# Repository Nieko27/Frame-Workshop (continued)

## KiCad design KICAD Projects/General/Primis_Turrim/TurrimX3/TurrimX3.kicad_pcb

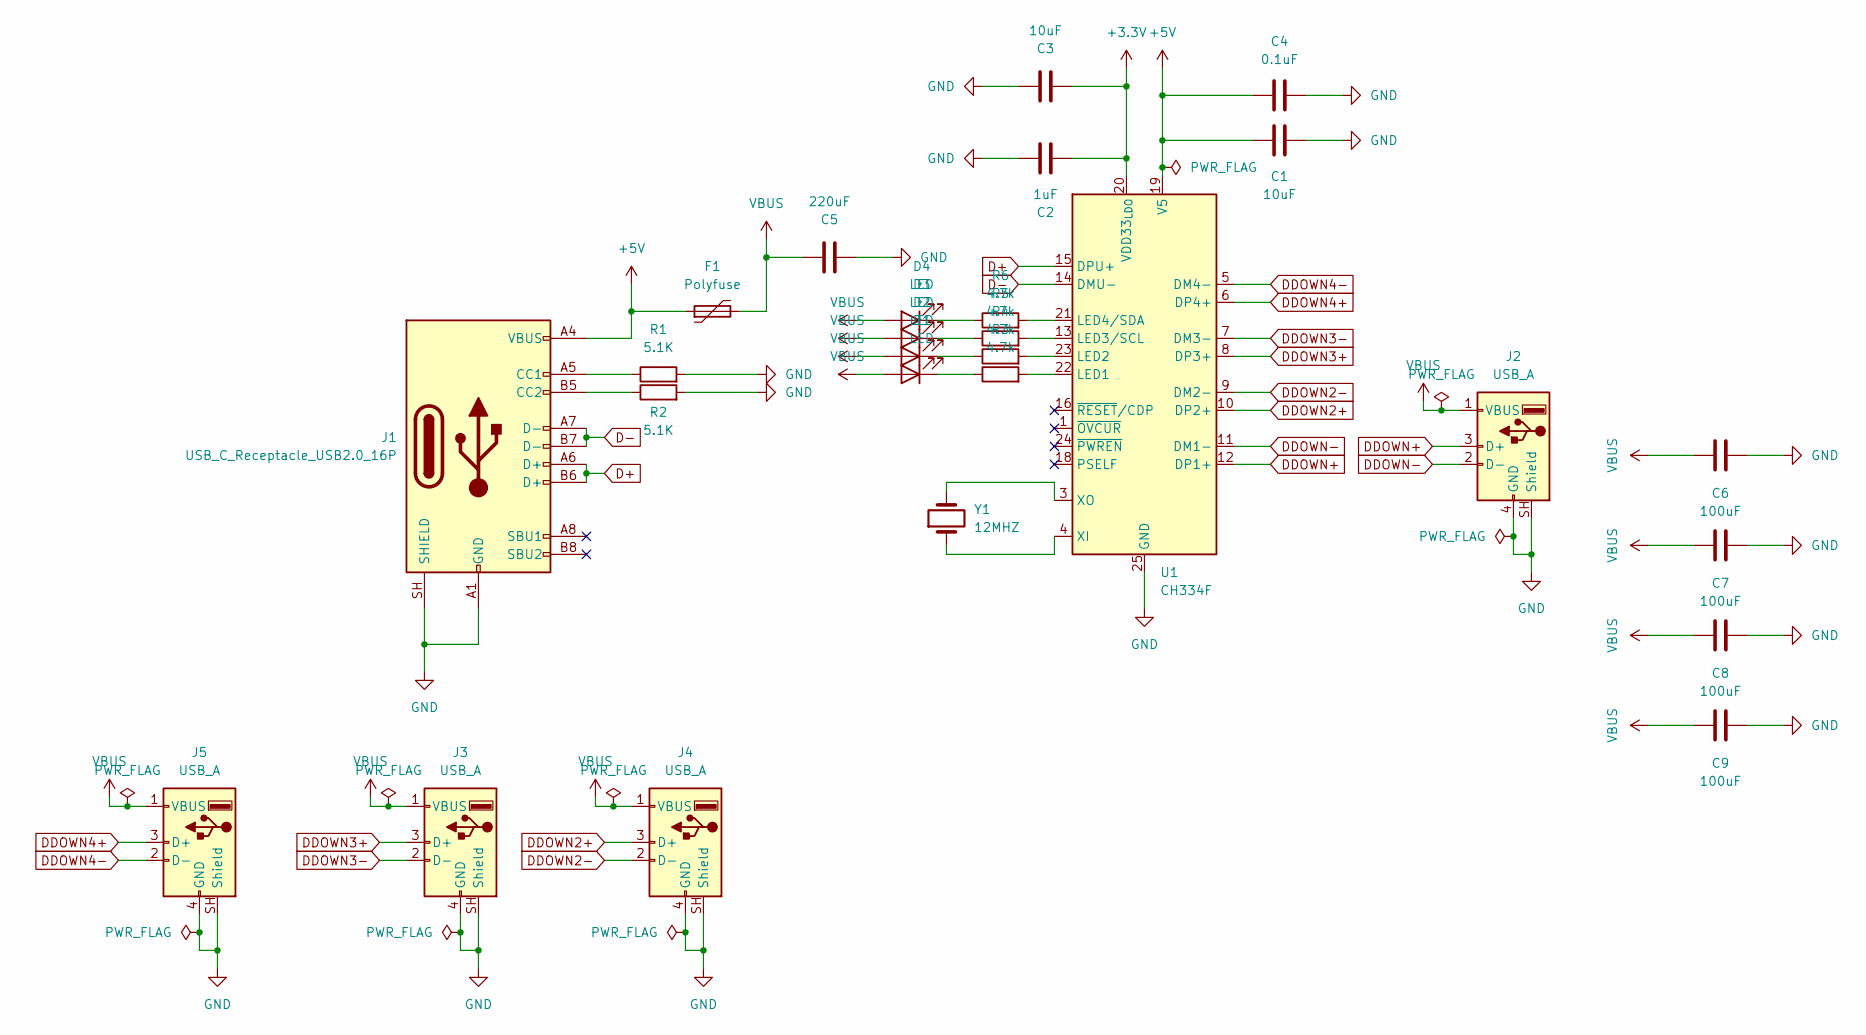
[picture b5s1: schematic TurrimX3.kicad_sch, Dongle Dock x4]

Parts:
C1, C3: 10uF; C_0805_2012Metric
C2: 1uF; C_0603_1608Metric
C4: 0.1uF; C_0603_1608Metric
C5: 220uF; C_0805_2012Metric
C6, C7, C8, C9: 100uF; C_0805_2012Metric
D1, D2, D3, D4: LED; LED_0603_1608Metric
F1: Polyfuse; Fuse_1206_3216Metric
J1: USB_C_Receptacle_USB2.0_16P; USB_C_Receptacle_HRO_TYPE-C-31-M-12
J2, J3, J4, J5: USB_A; USB_A_Molex_105057_Vertical
R1, R2: 5.1K; R_0805_2012Metric
R3, R4, R5, R6: 4.7k; R_0805_2012Metric
U1: CH334F; QFN-24-1EP_4x4mm_P0.5mm_EP2.7x2.7mm
Y1: 12MHZ; Crystal_SMD_2016-4Pin_2.0x1.6mm

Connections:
+3.3V: C2.1, C3.1, U1.20 (VDD33_{LDO})
+5V: C1.1, C4.1, F1.1, J1.A4 (VBUS), J1.A9 (VBUS), J1.B4 (VBUS), J1.B9 (VBUS), U1.19 (V5)
D+: J1.A6 (D+), J1.B6 (D+), U1.15 (DPU+)
D-: J1.A7 (D-), J1.B7 (D-), U1.14 (DMU-)
DDOWN2+: J4.3 (D+), U1.10 (DP2+)
DDOWN2-: J4.2 (D-), U1.9 (DM2-)
DDOWN3+: J3.3 (D+), U1.8 (DP3+)
DDOWN3-: J3.2 (D-), U1.7 (DM3-)
DDOWN4+: J5.3 (D+), U1.6 (DP4+)
DDOWN4-: J5.2 (D-), U1.5 (DM4-)
DDOWN+: J2.3 (D+), U1.12 (DP1+)
DDOWN-: J2.2 (D-), U1.11 (DM1-)
GND: C1.2, C2.2, C3.2, C4.2, C5.1, C6.2, C7.2, C8.2, C9.2, J1.A1 (GND), J1.A12 (GND), J1.B1 (GND), J1.B12 (GND), J1.SH (SHIELD), J2.4 (GND), J2.SH (Shield), J3.4 (GND), J3.SH (Shield), J4.4 (GND), J4.SH (Shield), J5.4 (GND), J5.SH (Shield), R1.2, R2.2, U1.25 (GND)
unnamed: D1.1 (K), R3.1
unnamed: D2.1 (K), R4.1
unnamed: D3.1 (K), R5.1
unnamed: D4.1 (K), R6.1
unnamed: J1.A5 (CC1), R1.1
unnamed: J1.B5 (CC2), R2.1
unnamed: R3.2, U1.22 (LED1)
unnamed: R4.2, U1.23 (LED2)
unnamed: R5.2, U1.13 (LED3/SCL)
unnamed: R6.2, U1.21 (LED4/SDA)
unnamed: U1.4 (XI), Y1.1
unnamed: U1.3 (XO), Y1.2
VBUS: C5.2, C6.1, C7.1, C8.1, C9.1, D1.2 (A), D2.2 (A), D3.2 (A), D4.2 (A), F1.2, J2.1 (VBUS), J3.1 (VBUS), J4.1 (VBUS), J5.1 (VBUS)

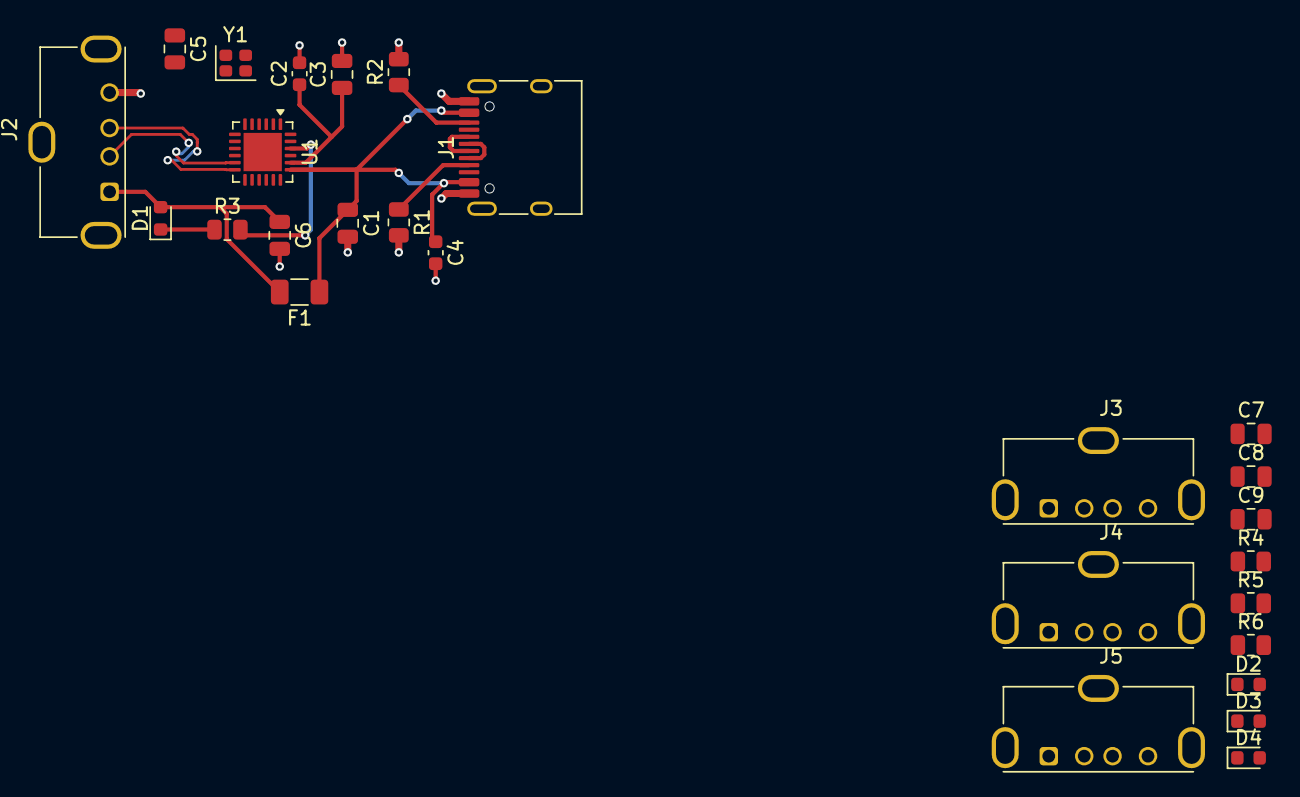
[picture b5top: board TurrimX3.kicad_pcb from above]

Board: 2 copper layers, 27 parts (0 on the bottom side), 26 nets.

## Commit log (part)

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2026-01-17 Clean
2026-01-17 Structure
2026-01-17 Structure2
2026-01-26 NameFix
2026-02-11 Face Tracker and Versipellis Clean
    -Organised the face tracker PCB a bit more
    -Added TODO to face tracker README
    -Organised Versipellis schematics
    -Updated images
2026-02-17 Gerbers plus clean up
    -Added gerbers for the face tracker and versipellis
    -Shrunk the face tracker and cleaned up
    -Fixed some DRC issues with both projects
2026-03-10 Quick Update
2026-04-26 FaceTracker fixes and Dongle rework
    -Fixed some mistakes on the Facetracker with the camera power lines.
    -Some part swaps and additions on the dongle to match the JLCPCBs catalogue
2026-04-27 Usb swap
    -Changed the dongle to another usb
2026-05-02 Dongle Cleanup
    -CLeanup before final
2026-05-02 Versipellis EV1 Final + General Github updates
    -Fixed a few remaining issues with Versipellis EV1
    -Created production files for Versipellis
    -Updated pictures for all projects
2026-05-13 Quick EV1 Dongle Fixes
    -Made some last minute fixes
2026-05-19 Organised + Added Turrim and Model
    -Added folder structure for all files types
    -Added general folder for small supplementary projects
    -Added Turrim (Dongle hub for Frame dongles)
    -Added PCB model for the Frame dongles
2026-05-26 Big Update
    -Added Versipellis pictures
    -Split Turrim into 2 versions, a simple, cheap 1 port version and a more complex 4 port hub version.
    -Started work on Locus
2026-05-26 Readme fix
2026-05-26 fix2
2026-06-25 VERSIPELLIS EV2 + TURRIM Production files
    -Swapped to a tag connect for programming VERSIPELLIS
    -Moved crystal closer to the NRF on VERSIPELLIS
    -Fixed swapped lines on usb on VERSIPELLIS
    -TURRIM cleanup and production files added
2026-06-29 VERSIPELLIS/TURRIM Model files
    -Added VERSIPELLIS EV2 model
    -Added TURRIM model
    -Added VERSIPELLIS case models
    -Update images
